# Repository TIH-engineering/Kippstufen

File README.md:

# Kippstufen

## 🔌 Leiterplattenbeschreibung

Die Leiterplatte **Kippstufen** dient zur Untersuchung verschiedener digitaler Grundschaltungen und Kippstufen. Sie wurde insbesondere für den Einsatz im Elektroniklabor und zur praktischen Ergänzung des Unterrichts entwickelt.

Auf der Leiterplatte sind unterschiedliche Schaltungsvarianten realisiert:

- **diskret aufgebaute Kippstufen** mit Transistoren
- **Kippstufe mit NE555-Timer**
- **bistabile Kippstufe** mit Logik-IC
- **monostabile Kippstufe** mit Logik-IC
- **astabile Kippstufe** mit Logik-IC

Über Taster und Steckverbinder können die Schaltungen angesteuert und unterschiedliche Betriebsarten untersucht werden. LEDs dienen zur optischen Anzeige der jeweiligen Ausgangszustände.

Bei der diskret aufgebauten Kippstufe ermöglichen Jumper die Konfiguration als **bistabile, monostabile oder astabile Kippstufe**. Zusätzlich sind Messanschlüsse vorgesehen, unter anderem zur Untersuchung der Kondensatorspannungen.

Die Leiterplatte eignet sich damit zur praktischen Untersuchung von **Schaltzuständen, Zeitverhalten, Rückkopplung und Oszillation** bei unterschiedlichen Realisierungen von Kippstufen.

> **Einsatzgebiet:** Laborübungen und Unterricht im Bereich Digitaltechnik / Elektronik

---

## 📥 Downloads

| Datei | Beschreibung |
|---|---|
| 📄 [Schaltplan (PDF)](../../releases/latest/download/schematic.pdf) | Schaltplan der Leiterplatte |
| 🖨️ [Leiterplatte (PDF)](../../releases/latest/download/pcb.pdf) | Leiterplattenansicht als PDF |
| 🔩 [Bohrplan (PDF)](../../releases/latest/download/drill.pdf) | Bohrdaten / Bohrplan |
| 📋 [Stückliste (Excel)](../../releases/latest/download/bom.xlsx) | Bill of Materials |
| 🌐 [Interactive BOM](../../releases/latest/download/ibom.html) | Interaktive Bestückungsansicht |
| 📦 [Fertigungsdaten](../../releases/latest/download/kicad.zip) | Gerber- und Bohrdaten |
| 🧊 [STEP-Modell](../../releases/latest/download/pcb.step) | 3D-Modell der Leiterplatte |

Die Dateien werden automatisch durch den Release-Workflow erzeugt.

---

## 🖥️ Leiterplatte

### Vorschau

| Oberseite | Unterseite |
|:---:|:---:|
|  |  |

### Oberseite

### Unterseite

---

## ℹ️ Projektinformationen

| Eigenschaft | Wert |
|---|---|
| **Projekt** | Kippstufen |
| **Software** | KiCad 10 |
| **Repository** | TIH-engineering/Kippstufen |
| **Autor** | TIH |
| **Lizenz** | CC BY-NC-SA 4.0 |

---

## 🗂️ Repository-Struktur

```text
.
├── .github/
│   └── workflows/       # GitHub Actions
├── .kibot/              # KiBot-Konfiguration
├── pcb/
│   ├── lib/             # Projektspezifische Bibliotheken
│   └── ...              # KiCad-Projektdateien
├── .gitignore
├── LICENSE
└── README.md

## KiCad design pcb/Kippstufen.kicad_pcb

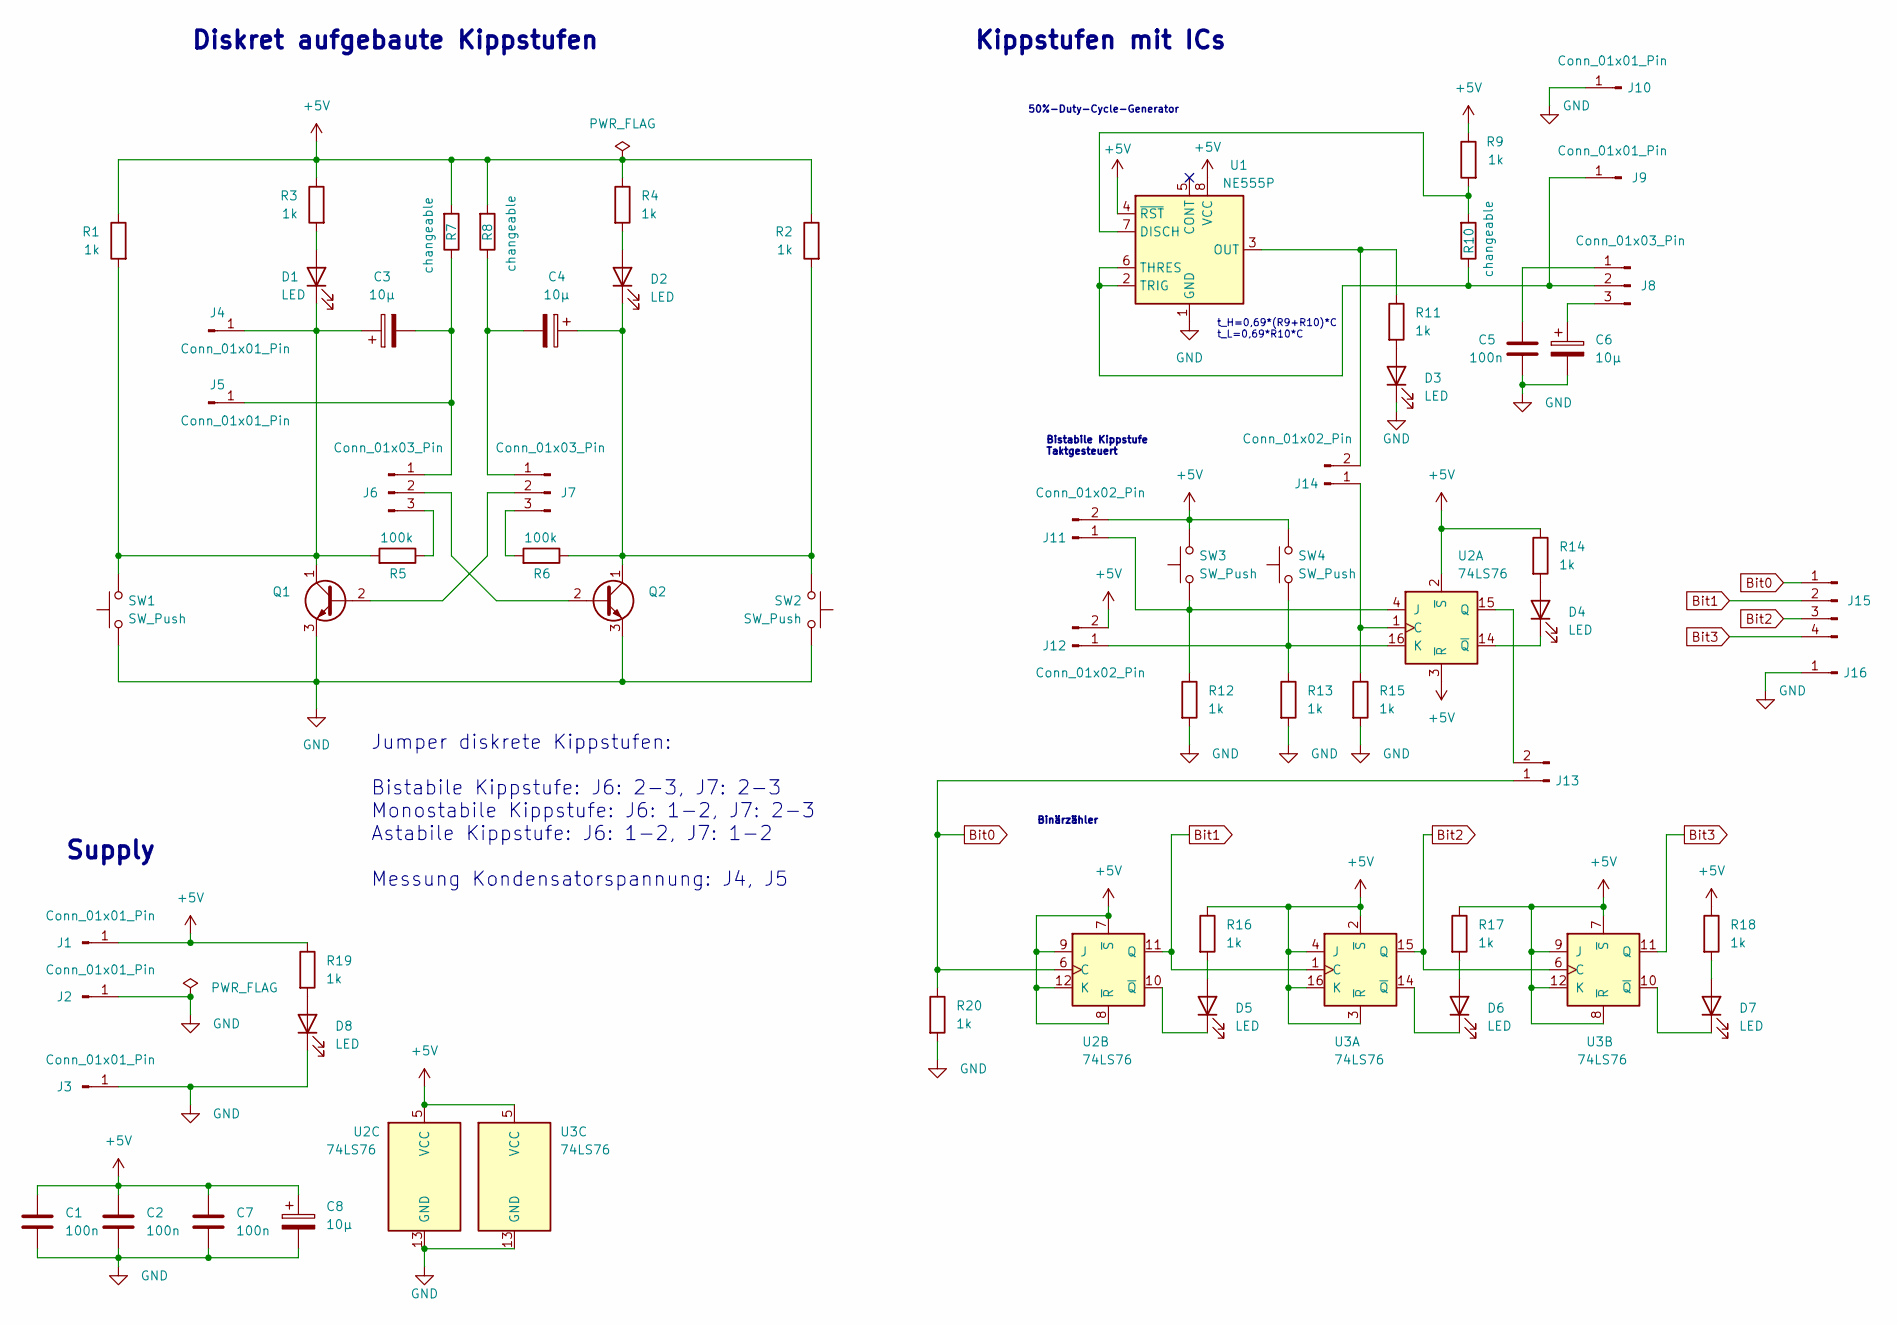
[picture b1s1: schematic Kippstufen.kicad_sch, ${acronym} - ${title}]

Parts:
C1, C2, C5, C7: 100n; C_1206_3216Metric
C3, C4, C6, C8: 10µ; CP_Radial_D5.0mm_P2.00mm
D1, D2, D3, D4, D5, D6, D7, D8: LED; LED_1206_3216Metric
J1, J2, J3, J4, J5, J9, J10, J16: Conn_01x01_Pin; PinHeader_1x01_P2.54mm_Vertical
J6, J7, J8: Conn_01x03_Pin; PinHeader_1x03_P2.54mm_Vertical
J11, J12, J13, J14: Conn_01x02_Pin; PinHeader_1x02_P2.54mm_Vertical
J15: Conn_01x04_Pin; PinHeader_1x04_P2.54mm_Vertical
Q1, Q2: BC547; TO-92_Inline_Wide
R1, R2, R3, R4, R9, R11, R12, R13, R14, R15, R16, R17, R18, R19, R20: 1k; R_1206_3216Metric
R5, R6: 100k; R_1206_3216Metric
R7, R8, R10: 10k; R_axial_SMD-Adapter_P10.16mm_1mm
SW1, SW2, SW3, SW4: SW_Push; SW_Push_1P1T_NO_E-Switch_TL3301NxxxxxG
U1: NE555P; DIP-8_W7.62mm
U2, U3: 74LS76; DIP-16_W7.62mm

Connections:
+5V: C1.1, C2.1, C7.1, C8.1, J1.1 (Pin_1_1), J11.2, J12.2, R1.1, R2.1, R3.1, R4.1, R7.2, R8.2, R9.1, R14.1, R16.1, R17.1, R18.1, R19.1, SW3.2, SW4.2, U1.4 (~RST), U1.8 (VCC), U2.2 (~S), U2.3 (~R), U2.5 (VCC), U2.7 (~S), U2.8 (~R), U2.9 (J), U2.12 (K), U3.2 (~S), U3.3 (~R), U3.4 (J), U3.5 (VCC), U3.7 (~S), U3.8 (~R), U3.9 (J), U3.12 (K), U3.16 (K)
Bit0: J13.1, J15.1, R20.1, U2.6 (C)
Bit1: J15.2, U2.11 (Q), U3.1 (C)
Bit2: J15.3, U3.6 (C), U3.15 (Q)
Bit3: J15.4, U3.11 (Q)
GND: C1.2, C2.2, C5.2, C6.2, C7.2, C8.2, D3.1 (K), D8.1 (K), J2.1 (Pin_1_1), J3.1 (Pin_1_1), J10.1 (Pin_1_1), J16.1 (Pin_1_1), Q1.3 (E), Q2.3 (E), R12.2, R13.2, R15.2, R20.2, SW1.1, SW2.1, U1.1 (GND), U2.13 (GND), U3.13 (GND)
unnamed: D1.2 (A), R3.2
unnamed: C3.1, D1.1 (K), J4.1 (Pin_1_1), Q1.1 (C), R1.2, R5.2, SW1.2
unnamed: D2.2 (A), R4.2
unnamed: C4.1, D2.1 (K), Q2.1 (C), R2.2, R6.1, SW2.2
unnamed: D3.2 (A), R11.2
unnamed: D4.2 (A), R14.2
unnamed: D4.1 (K), U2.14 (~Q)
unnamed: D5.2 (A), R16.2
unnamed: D5.1 (K), U2.10 (~Q)
unnamed: D6.2 (A), R17.2
unnamed: D6.1 (K), U3.14 (~Q)
unnamed: D7.2 (A), R18.2
unnamed: D7.1 (K), U3.10 (~Q)
unnamed: D8.2 (A), R19.2
unnamed: C3.2, J5.1 (Pin_1_1), J6.1, R7.1
unnamed: J6.2, Q2.2 (B)
unnamed: J6.3, R5.1
unnamed: C4.2, J7.1, R8.1
unnamed: J7.2, Q1.2 (B)
unnamed: J7.3, R6.2
unnamed: C5.1, J8.1
unnamed: J8.2, J9.1 (Pin_1_1), R10.1, U1.2 (TRIG), U1.6 (THRES)
unnamed: C6.1, J8.3
unnamed: J11.1, R12.1, SW3.1, U2.4 (J)
unnamed: J12.1, R13.1, SW4.1, U2.16 (K)
unnamed: J13.2, U2.15 (Q)
unnamed: J14.1, R15.1, U2.1 (C)
unnamed: J14.2, R11.1, U1.3 (OUT)
unnamed: R9.2, R10.2, U1.7 (DISCH)

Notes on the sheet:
Bistabile Kippstufe Taktgesteuert
Binärzähler
Supply
t_H=0,69*(R9+R10)*C t_L=0,69*R10*C
50%-Duty-Cycle-Generator
Jumper diskrete Kippstufen: Bistabile Kippstufe: J6: 2-3, J7: 2-3 Monostabile Kippstufe: J6: 1-2, J7: 2-3 Astabile Kippstufe: J6: 1-2, J7: 1-2 Messung Kondensatorspannung: J4, J5
Diskret aufgebaute Kippstufen
Kippstufen mit ICs

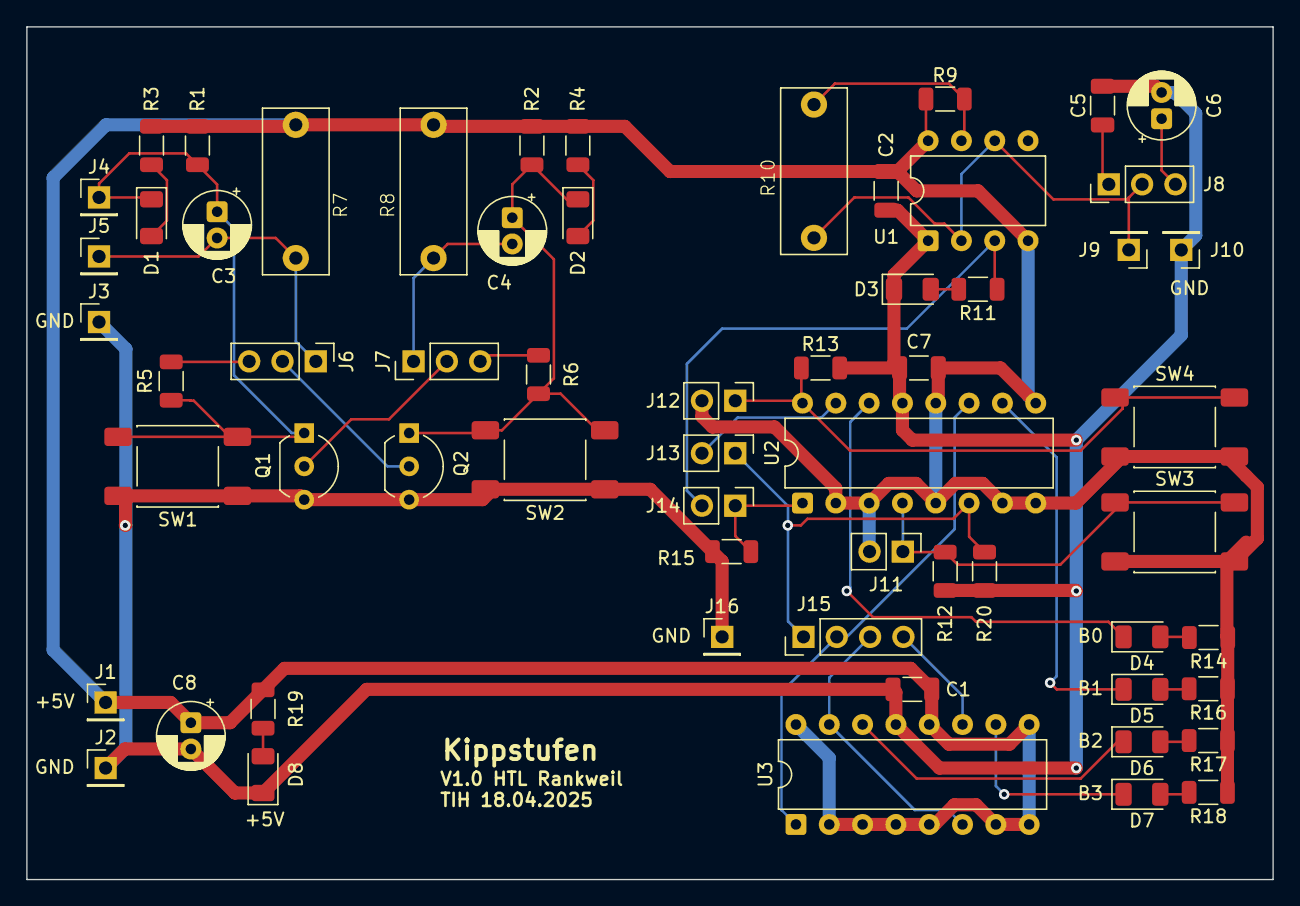
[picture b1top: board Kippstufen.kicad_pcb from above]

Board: 2 copper layers, 95.0 x 65.0 mm, 61 parts (0 on the bottom side), 35 nets.

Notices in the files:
README.md:
License: CC-BY-NC-SA-4.0
